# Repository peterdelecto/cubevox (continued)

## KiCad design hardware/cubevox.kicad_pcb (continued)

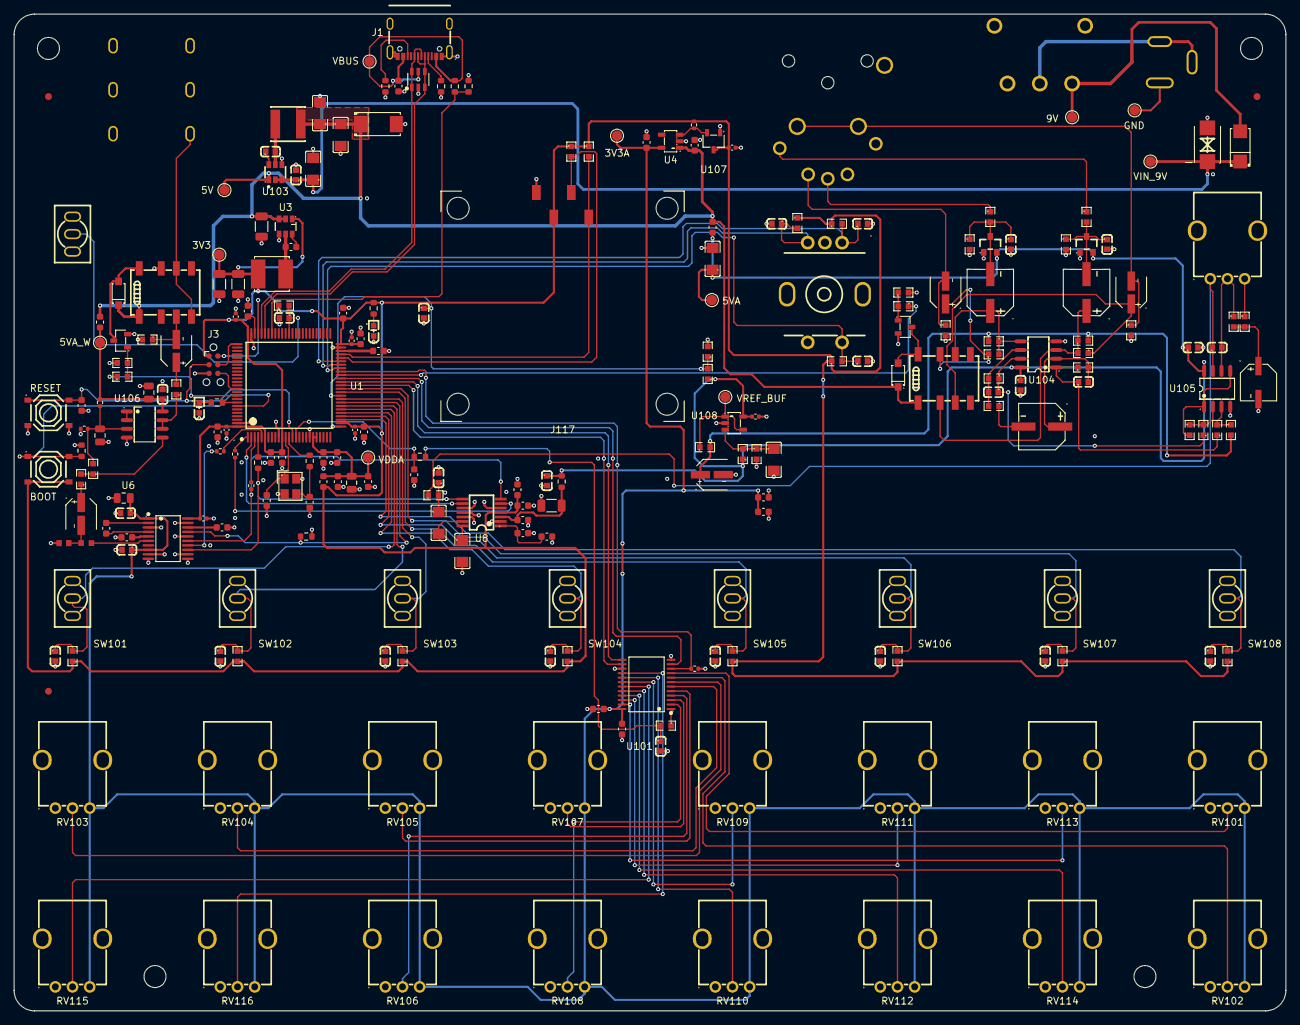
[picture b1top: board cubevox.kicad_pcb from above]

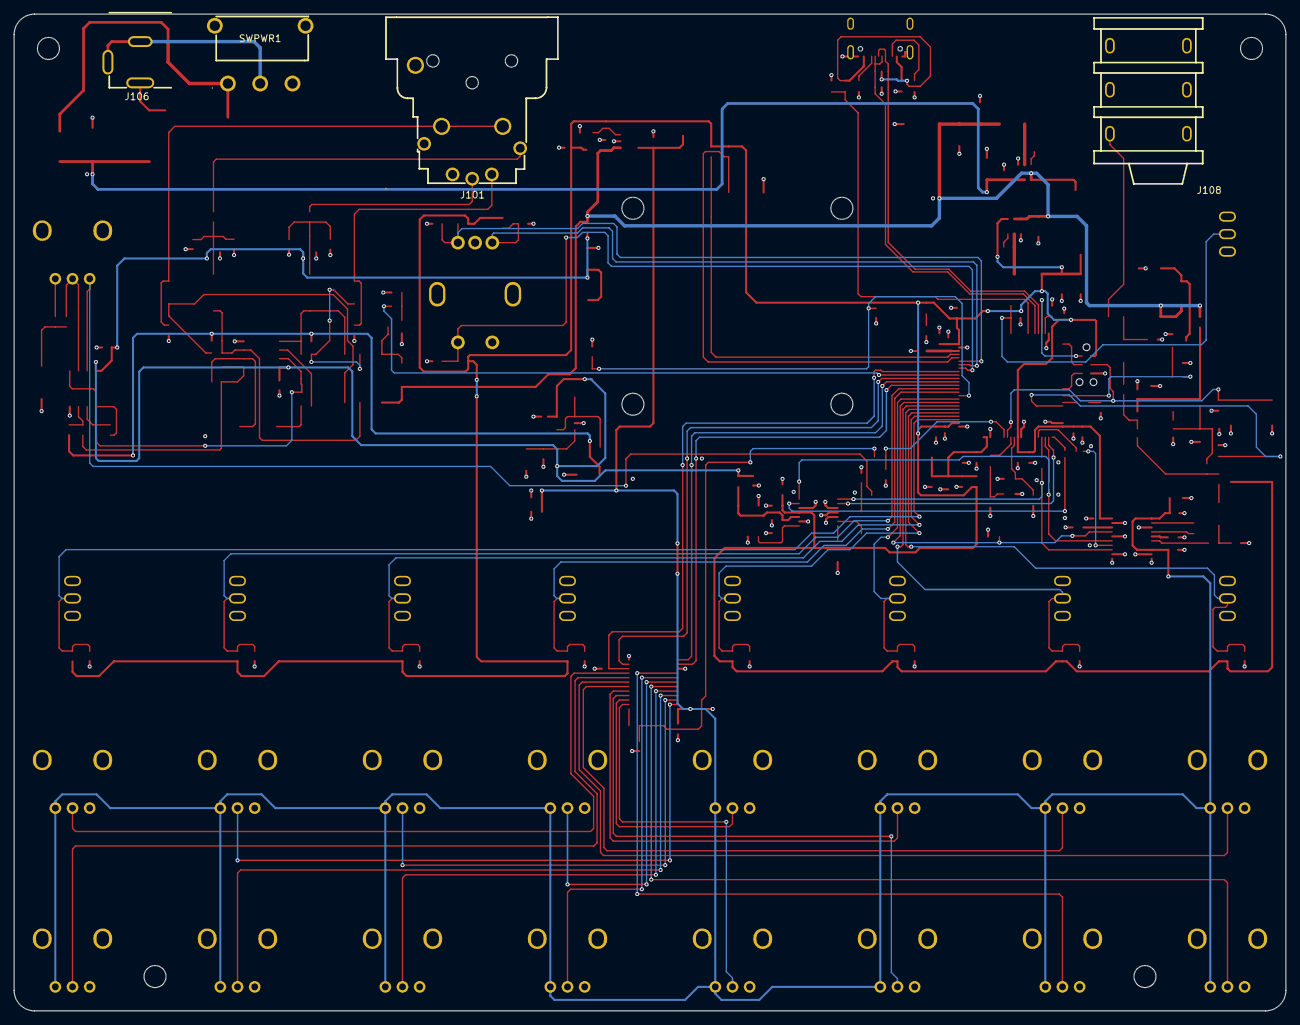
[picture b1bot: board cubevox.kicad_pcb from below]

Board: 4 copper layers, 185.0 x 145.0 mm, 246 parts (4 on the bottom side), 132 nets.

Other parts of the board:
FID1, FID2, FID3: Fiducial_1mm_Mask2mm

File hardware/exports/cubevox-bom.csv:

"Reference","Value","Footprint","LCSC","Datasheet"
"C2-C4,C7,C9,C11,C14,C23,C27,C29,C33,C45,C47,C49","100nF","Capacitor_SMD:C_0603_1608Metric","C14663",""
"C6","4.7uF","Capacitor_SMD:C_0603_1608Metric","C19666",""
"C8,C10,C24","1uF","Capacitor_SMD:C_0603_1608Metric","C15849",""
"C12,C13,C25,C34,C35","2.2uF","Capacitor_SMD:C_0603_1608Metric","C23630",""
"C15,C16","15pF","Capacitor_SMD:C_0603_1608Metric","C1644",""
"C18","1uF","Capacitor_SMD:C_0603_1608Metric","C90540",""
"C19","100uF 10V","Capacitor_Tantalum_SMD:CP_EIA-6032-28_Kemet-C","C8649",""
"C20-C22,C44","22uF","Capacitor_SMD:C_1206_3216Metric","C12891",""
"C28,C30,C32,C46,C48","10uF","Capacitor_SMD:C_0603_1608Metric","C19702",""
"C55","1nF","Capacitor_SMD:C_0603_1608Metric","C1588",""
"C56,C58","10nF","Capacitor_SMD:C_0402_1005Metric","C15195",""
"C57,C61,C165-C167","100nF","Capacitor_SMD:C_0402_1005Metric","C1525",""
"C101,C113,C116,C118,C127,C130,C134,C143-C157,C162,C163","100nF","cubevox:C0603","C14663",""
"C111","2.2uF","cubevox:C0603","C23630",""
"C112,C114,C115","22uF","cubevox:C1206","C12891",""
"C117,C135,C137,C138","10uF","cubevox:C1206","C14860",""
"C119,C123","100pF","cubevox:C0603","C14858",""
"C120,C124","47uF 25V","cubevox:CAP-SMD_BD6.3-L6.6-W6.6-LS7.6-FD","C72521",""
"C121,C125,C139,C141,C160","10uF 25V","cubevox:CAP-SMD_BD4.0-L4.3-W4.3-FD","C72484",""
"C128,C129,C132","47pF","cubevox:C0603","C1671",""
"C136,C161","2.2nF","cubevox:C0603","C2991172",""
"C142","10nF","cubevox:C0603","C57112",""
"C158","22uF 25V NP","cubevox:CAP-SMD_BD6.3-L6.6-W6.6-FD","C413679",""
"C159","100uF 10V","cubevox:CAP-SMD_BD5.0-L5.3-W5.3-LS6.3-FD","C191859",""
"C164,C168,C169","10uF","Capacitor_SMD:C_0805_2012Metric","C15850",""
"D1","USER red","cubevox_h7core:LED-SMD_L1.6-W0.8-R-RD","C2286",""
"D2","USBLC6-2SC6","cubevox_h7core:SOT-23-6_L2.9-W1.6-P0.95-LS2.8-BL","C2687116",""
"D3","PWR red","cubevox_h7core:LED-SMD_L1.6-W0.8-R-RD","C2286",""
"D104,D109","1N4148W","cubevox:SOD-123F_L2.7-W1.6-LS3.8-RD","C81598",""
"D105","SMBJ15CA","cubevox:SMB_L4.4-W3.6-LS5.4-BI","C19077570",""
"D106","SS34","cubevox:SMA_L4.3-W2.6-LS5.2-RD","C8678",""
"D107,D108","BAT54S","cubevox_h7core:SOT-23_L2.9-W1.3-P1.90-LS2.4-BR","C19726",""
"ENC101","EC11E15244B2","cubevox:SW-TH_EC11E","C470754",""
"ENC102,ENC103","EC11E15204A3","cubevox:SW-TH_EC11E","C470710",""
"FB1,FB101,FB102","120R@100MHz","Inductor_SMD:L_0603_1608Metric","C14709",""
"J1","USB-C","cubevox_h7core:USB-C-SMD_TYPE-C16PIN","C393939",""
"J101","J_IN NCJ6FA-H","cubevox:CONN-TH_NCJ6FA-H","C368458",""
"J106","DC 9V","cubevox:DC-IN-TH_PJ-002A","C3096082",""
"J108","OUT 6.35mm","cubevox:AUDIO-TH_PJ-611E_1","C309282",""
"J117","OLED SH1106","cubevox:OLED-1.3-SH1106-I2C-4P","C42379197",""
"K101,K102","G6K-2F-Y DC5","cubevox:RELAY-SMD_G6K-2F-X-XX","C47190",""
"L1","3.9uH","cubevox_h7core:IND-SMD_L5.0-W5.0","C7427132",""
"L101","4.7uH","cubevox:IND-SMD_L5.0-W5.0_ANR5040T","C7427135",""
"Q101","MMBT3904","cubevox:SOT-23-3_L2.9-W1.3-P1.90-LS2.4-BR","C20526",""
"R1","0R","Resistor_SMD:R_0603_1608Metric","C21189",""
"R2,R16","10k","Resistor_SMD:R_0603_1608Metric","C25804",""
"R3,R10","680R","Resistor_SMD:R_0603_1608Metric","C23228",""
"R4,R5","5.1k","Resistor_SMD:R_0603_1608Metric","C23186",""
"R6","33k","Resistor_SMD:R_0603_1608Metric","C4216",""
"R7","82k","Resistor_SMD:R_0603_1608Metric","C23254",""
"R20","10R","Resistor_SMD:R_0603_1608Metric","C22859",""
"R27,R156,R157","33R","Resistor_SMD:R_0402_1005Metric","C25105",""
"R29","33R","Resistor_SMD:R_0603_1608Metric","C23140",""
"R30","100R","Resistor_SMD:R_0603_1608Metric","C22775",""
"R101,R104","47R","cubevox:R0603","C23182",""
"R102,R105","22k","cubevox:R0603","C31850",""
"R103,R106","1.2k","cubevox:R0603","C22765",""
"R108,R110","4.53k","cubevox:R0603","C25971",""
"R109,R126,R150","1k","cubevox:R0603","C21190",""
"R111-R114","10k 0.1%","cubevox:R0603","C309083",""
"R116","330R","cubevox:R0603","C23138",""
"R117,R118,R120,R122,R127-R141,R151,R152","10k","cubevox:R0603","C25804",""
"R119,R124","100R","cubevox:R0603","C22775",""
"R123","15k","cubevox:R0603","C22809",""
"R125,R144,R145,R148,R149,R153","100k","cubevox:R0603","C25803",""
"R142,R143","4.7k","cubevox:R0603","C23162",""
"R146","22R","cubevox:R0603","C23345",""
"R147","470R","cubevox:R0603","C23179",""
"R154,R155","10k","Resistor_SMD:R_0402_1005Metric","C25744",""
"RV101-RV114","10k","cubevox:RES-ADJ-TH_RK09D1130C2P","C361173",""
"RVGAIN1","10k GAIN","cubevox:RES-ADJ-TH_RK09D1130C2P","C361173",""
"SW101-SW108,SWBYPASS1","ST-0-102 bat toggle","cubevox:SW-TH_3P-L8.3-W5.2-P2.54_ST-0-102-A01-T000","C1788487",""
"SWBOOT1","BOOT0","cubevox_h7core:SW-SMD_4P-L5.1-W5.1-P3.70-LS6.5-TL_H1.5","C318884",""
"SWRESET1","RESET","cubevox_h7core:SW-SMD_4P-L5.1-W5.1-P3.70-LS6.5-TL_H1.5","C318884",""
"U1","STM32H743VIT6","cubevox_h7core:LQFP-100_L14.0-W14.0-P0.50-LS16.0-BL","C114409",""
"U3","AP63203WU-7","cubevox_h7core:TSOT-26_L2.9-W1.6-P0.95-LS2.8-BL","C780769",""
"U4","TLV75533PDBVR","cubevox_h7core:SOT-23-5_L3.0-W1.7-P0.95-LS2.8-BR","C404027",""
"U6","PCM5102APWR","cubevox_h7core:TSSOP-20_L6.5-W4.4-P0.65-LS6.4-BL","C107671",""
"U8","PCM1808PWR","cubevox_h7core:TSSOP-14_L5.0-W4.4-P0.65-LS6.4-BL","C55513",""
"U101","CD74HC4067","cubevox:SSOP-24_L8.1-W5.3-P0.65-LS7.8-BL","C98457",""
"U103","AP63205WU-7","cubevox:TSOT-23-6_L2.9-W1.6-P0.95-LS2.8-BL","C2071056",""
"U104-U106","OPA2197IDR","cubevox:SOIC-8_L4.9-W3.9-P1.27-LS6.0-BL","C139363",""
"U107","SP809EK-L-2-9/TR","Package_TO_SOT_SMD:SOT-23","C412495",""
"U108","OPA197IDBVR","Package_TO_SOT_SMD:SOT-23-5","C221351",""
"Y1","25MHz 12pF","cubevox_h7core:CRYSTAL-SMD_4P-L3.2-W2.5-BL","C9006",""

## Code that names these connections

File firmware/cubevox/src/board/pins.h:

// cubevox pin constants. Source of truth is hardware/PINMAP.md (U1, STM32H743VIT6).
// Net names follow the schematic.

#pragma once

#include <Arduino.h>

#include <array>

namespace pins {

// GPIO register access for code that cannot call HAL (fault handler, bulk init). The pin
// constants below are Arduino pin indexes, so each decode goes through digitalPin[], a const table
// in flash with no HAL state, which makes it safe inside a fault handler.
inline uint32_t portIndexOf(uint32_t pin) { return STM_PORT(digitalPinToPinName(pin)); }
inline GPIO_TypeDef* portOf(uint32_t pin) {
  return reinterpret_cast<GPIO_TypeDef*>(GPIOA_BASE + (GPIOB_BASE - GPIOA_BASE) * portIndexOf(pin));
}
inline uint32_t maskOf(uint32_t pin) { return 1u << STM_PIN(digitalPinToPinName(pin)); }

// Pot mux (CD74HC4067 on 3V3A). Keep the selects low until 3V3A is up, and at the lowest GPIO speed.
constexpr uint32_t kMuxS0 = PE12;  // MUX_S0
constexpr uint32_t kMuxS1 = PE10;  // MUX_S1
constexpr uint32_t kMuxS2 = PE8;   // MUX_S2
constexpr uint32_t kMuxS3 = PE9;   // MUX_S3
constexpr uint32_t kPotMuxOut = PC0;  // POT_MUX_OUT (MUX1_SIG_ADC), ADC1/2/3_INP10, 100 R / 1 nF at the pin
constexpr uint32_t kPotMuxAdcChannel = ADC_CHANNEL_10;  // INP10 of whichever ADC reads kPotMuxOut

// Slot bypass toggles, 10 k pull-up and 100 nF on the board, one throw to GND.
constexpr uint32_t kToggle1 = PA7;  // TOGGLE1
constexpr uint32_t kToggle2 = PC4;  // TOGGLE2
constexpr uint32_t kToggle3 = PB0;  // TOGGLE3
constexpr uint32_t kToggle4 = PA6;  // TOGGLE4
constexpr uint32_t kToggle5 = PB2;  // TOGGLE5
constexpr uint32_t kToggle6 = PA5;  // TOGGLE6
constexpr uint32_t kToggle7 = PE7;  // TOGGLE7
constexpr uint32_t kToggle8 = PA4;  // TOGGLE8

// Global mute and output stage.
constexpr uint32_t kMuteSw = PC6;  // MUTE_SW, low = muted, R120 pull-up on the board
constexpr uint32_t kMuteN = PB5;   // MUTE_N, high closes relay K102, low at reset
constexpr uint32_t kXsmt = PC5;    // XSMT, PCM5102A soft mute, low = muted, R16 pull-down

// Input pad relay K103.
constexpr uint32_t kPadEn = PE11;  // PAD_EN, output, high = LINE (pad in circuit), default low = MIC

// Indicators and sense.
constexpr uint32_t kUserLed = PB7;   // USER_LED
constexpr uint32_t kVbusSense = PA9;  // VBUS_SENSE, R6/R7 divider, native OTG sensing off
constexpr uint32_t kVaSense = PB1;    // VA_SENSE, 5VA through 10 k / 10 k, 100 nF at the pin, ADC12_INP5
constexpr uint32_t kVaSenseAdcChannel = ADC_CHANNEL_5;

// USB OTG_FS data pins as PinName, because the core's PinMap_USB_OTG_FS table takes those.
constexpr PinName kUsbDm = PA_11;  // USB_DM
constexpr PinName kUsbDp = PA_12;  // USB_DP

// OLED on I2C2 (AF4), SH1106, 4.7 k pull-ups on the board.
constexpr uint32_t kOledScl = PB10;  // I2C_SCL
constexpr uint32_t kOledSda = PB11;  // I2C_SDA

// MENU encoder, EXTI lines 13, 14, 15.
constexpr uint32_t kEncMenuA = PE15;   // ENC_MENU_A
constexpr uint32_t kEncMenuB = PE14;   // ENC_MENU_B
constexpr uint32_t kEncMenuSw = PE13;  // ENC_MENU_SW

// SAI1, AF6, all on port E. Owned by the audio driver (HAL).
constexpr uint32_t kSaiMclkA = PE2;  // MCLK_A (ADC_SCKI_SRC)
constexpr uint32_t kSaiSdB = PE3;    // SD_B (ADC_DOUT)
constexpr uint32_t kSaiFsA = PE4;    // FS_A (I2S_LRCLK)
constexpr uint32_t kSaiSckA = PE5;   // SCK_A (I2S_BCLK_SRC)
constexpr uint32_t kSaiSdA = PE6;    // SD_A (I2S_DATA)
constexpr std::array<uint32_t, 5> kSaiPins = {kSaiMclkA, kSaiSdB, kSaiFsA, kSaiSckA, kSaiSdA};

// BOOT0 (pin 94) is the DFU recovery button, not a GPIO the firmware uses.
// PB8, PB9 and PE0 are spare. PB6, PE1 and PB4 are unconnected.

// Boot report line: the port letter and bit that portOf / maskOf decode for the pins driven by
// register, so a misdecode shows on the first board.
void report(Print& out);

}  // namespace pins

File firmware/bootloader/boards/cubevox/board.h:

// TinyUF2 board for cubevox: STM32H743VIT6, 25 MHz crystal, TinyUF2 in bank 1 sector 0 and the
// application from CV_APP_START. Addresses, magics and ids come from boot_block.h.

#ifndef BOARD_H_
#define BOARD_H_

#include "boot_block.h"
#include "clock.h"

#ifdef __cplusplus
extern "C" {
#endif

// Shown in INFO_UF2.TXT and DIAG.TXT. Bumped with every bootloader change; independent of
// VERSION.txt because the two programs ship on different paths.
#define CV_BOOT_VERSION "0.09"

//--------------------------------------------------------------------+
// Board identity
//--------------------------------------------------------------------+

// USER_LED (pins.h kUserLed). The sealed box has no reset button Adam can reach, so no double
// tap: the 500 ms wait would cost every boot for nothing.
#define LED_PORT             GPIOB
#define LED_PIN              GPIO_PIN_7
#define TINYUF2_DBL_TAP_DFU  0
#define UF2_BOARD_ID         "cubevox-h743-v4"
#define UF2_VOLUME_LABEL     "CUBEVOX"
#define LED_STATE_ON         1

//--------------------------------------------------------------------+
// Flash
//--------------------------------------------------------------------+

// The port writes [BOARD_FLASH_APP_START, FLASH_BANK1_BASE + BOARD_FLASH_SIZE). Ending that at
// CV_APP_END keeps every UF2 write in bank 1; bank 2 holds the layout record and Adam's data.
#define BOARD_FLASH_APP_START  CV_APP_START
#define BOARD_FLASH_SIZE       (CV_APP_END - FLASH_BANK1_BASE)

//--------------------------------------------------------------------+
// USB UF2
//--------------------------------------------------------------------+

#define USB_VID              CV_USB_VID_BOOT
#define USB_PID              CV_USB_PID_BOOT
#define USB_MANUFACTURER     "cubevox"
#define USB_PRODUCT          "cubevox update"
#define UF2_PRODUCT_NAME     "cubevox"

// OTG_FS on PA11/PA12. The box is self-powered and PA9 is not OTG VBUS, so the port's B-session
// override keeps the core attached and board_hooks.c senses the cable on VBUS_SENSE (pins.h
// kVbusSense, the R6/R7 divider) as a plain input, as the application's usb_link.cpp does. Its
// debounce and the restart's wait after an eject are policy, in boot_decide.h.
#define USB_NO_VBUS_PIN      1
#define BOARD_TUD_RHPORT     0
#define CV_VBUS_PORT         GPIOA
#define CV_VBUS_PIN          GPIO_PIN_9

// The drive serves INFO_UF2.TXT and DIAG.TXT only (diag.c). Every UF2 block passes
// board_uf2_block_accept() and reports its write to board_uf2_block_written(), and every root
// directory sector the host writes reaches board_uf2_dir_written() (board_hooks.c). Both files
// have a fixed size, so the directory never changes while their text does.
#define TINYUF2_INDEX_HTM           0
#define TINYUF2_CURRENT_UF2         0
#define TINYUF2_BOARD_INFO_UF2      1
#define TINYUF2_BOARD_BLOCK_FILTER  1
#define TINYUF2_BOARD_DIR_HOOK      1
#define CV_INFO_TEXT_BYTES          512u
#define CV_DIAG_TEXT_BYTES          4096u
extern char cvDiagText[CV_DIAG_TEXT_BYTES];
#define TINYUF2_BOARD_FILES {.name = "DIAG    TXT", .content = cvDiagText, .size = CV_DIAG_TEXT_BYTES},

#ifdef __cplusplus
}
#endif

#endif

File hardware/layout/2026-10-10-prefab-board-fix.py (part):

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
  <kicad python3> -I hardware/layout/2026-10-10-prefab-board-fix.py hardware/cubevox.kicad_pcb [--apply]

1. K103 pad contacts on the NC pins: IN_P to pad 2, LINE_N to pad 7, pads 4/5 open. IN_N stays
   on COM pad 6. The relay pads are 1.0 mm wide and 2.1 mm tall.
2. C127 feeds U105.8 on F.Cu; the B.Cu jog between the two 5VA vias goes.
3. The GND via inside D2.2 goes (the pad keeps its via 0.94 mm south).
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
def pass3(path, apply):
    """Owner moved R162 east of U101.10. Make pad 1 the corner (S0 vertical in from the north, straight
    west into pin 10), drop the off-pad T, merge the collinear MUX_S0 split left at the old spot."""
    b = pcbnew.LoadBoard(path)
    x = Fix2(b)
    x.say('7. R162 pad 1 as the MUX_S0 corner')
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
